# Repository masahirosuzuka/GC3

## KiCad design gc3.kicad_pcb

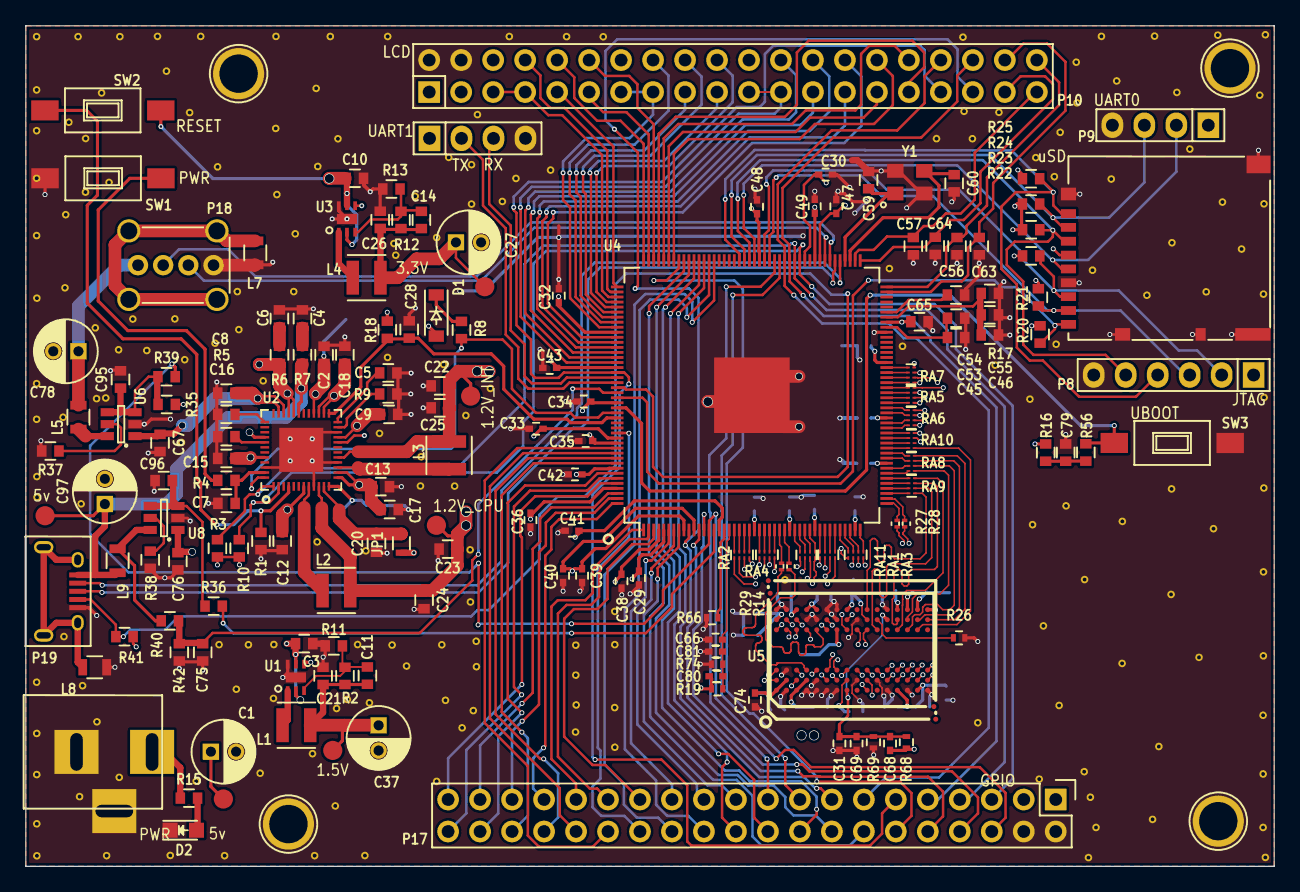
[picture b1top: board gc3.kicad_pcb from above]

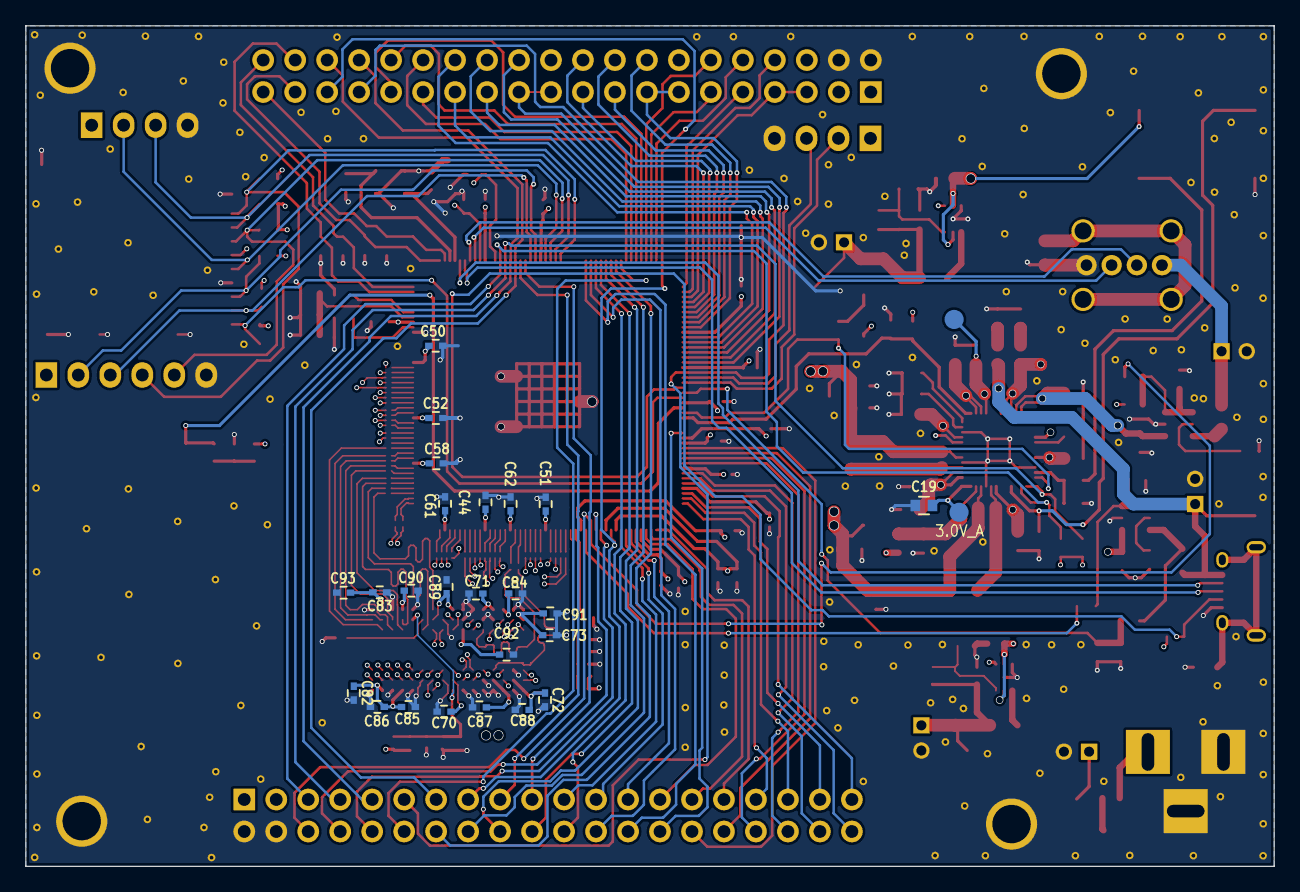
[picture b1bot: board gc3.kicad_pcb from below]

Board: 6 copper layers, 99.1 x 66.8 mm, 191 parts (26 on the bottom side), 225 nets.

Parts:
C1, C27, C37, C78, C97: 100uF; C_Radial_D5_L11_P2
C2, C9, C56, C57, C63, C64, C79: 1uF; Common_0603
C3, C10: 4.7uF; Common_0603
C4, C5, C6, C8, C12, C13, C15, C16, C17, C18, C19, C20, C22, C23, C55: 10uF/6.3V; Common_0603
C7, C24, C25: 1nF; Common_0603
C11, C14: 22pF; Common_0603
C21, C26: 10uF; Common_0603
C28, C67, C75, C76, C95, C96: 0.1uF; Common_0603
C29, C30, C32, C33, C34, C35, C38, C40, C43, C44, C52, C61: 0.1uF/6.3V; C_0402
C31, C47, C66, C68, C69, C70, C71, C72, C73, C74, C80, C81, C83, C84, C85, C86, C88, C89, C90, C91, C92, C93: 0.1uF; C_0402
C36, C39, C41, C48, C50, C58, C62: 10uF/6.3V; C_0402
C42, C49, C51, C82, C87: 22uF/6.3V; C_0402
C45, C46, C53, C54: 0.1uF/6.3V; Common_0603
C59, C60: 30pF; Common_0603
C65: 22uF/6.3V; Common_0603
D1: DIODE; SOD-123
D2: POWER; LED-0805
J1: JACK; BARREL_JACK
J2: DM3AT-SF-PEJM5
JP1: JUMPER; R_0603
L1, L2, L3, L4: 2.2uH; Neosid_Inductor_SMS-ME3015
L5, L7, L8, L9: FB/2A; R_0805
P1, P2, P3, P4, P5, P6, P15: TESTPOINT; Measurement_Point_Round-SMD-Pad_Small
P7: LCD; Pin_Header_Straight_2x20
P8: JTAG; Pin_Header_Straight_1x06
P9: UART0; Pin_Header_Straight_1x04
P10: UART1; Pin_Header_Straight_1x04
P11, P12, P13, P14: GND; 1pin
P16: TEESTPOINT; Measurement_Point_Round-SMD-Pad_Small
P17: GPIO; Pin_Header_Straight_2x20
P18: USB_A; USB_A_Vertical
P19: USB_OTG; USB_Micro-B
R1: 510R; Common_0603
R2: 315k; Common_0603
R3, R10: 2.2k; Common_0603
R4: 1k; Common_0603
R5: 240R/1%; Common_0603
R6, R7: 1R; Common_0603
R8, R18, R20, R21, R22, R23, R24, R25, R35, R41: 47k; Common_0603
R9, R17: 200k/1%; Common_0603
R11: 210k; Common_0603
R12, R36, R39: 100k; Common_0603
R13: 22k; Common_0603
R14, R29: 22R; R_0201
R15: 90R; Common_0603
R16: 100k/1%; Common_0603
R19, R68, R69, R74: 2k/1%; R_0402
R26, R66: 240R/1%; R_0402
R27, R28: 24R; R_0201
R37, R38: 20k; Common_0603
R40: 47K; Common_0603
R42: 100K; Common_0603
R56: 6.8k/1%; Common_0603
RA1, RA2, RA3, RA4, RA5, RA6, RA7, RA8, RA9, RA10, RA11: 22R; EXB18V
SW1: PWR_ON; SW_SPST_FSMSM
SW2: RESET; SW_SPST_FSMSM
SW3: UBOOT; SW_SPST_FSMSM
U1, U3: TPS62290
U2: axp209; TQFP-48-1EP_6x6mm_Pitch0.4mm
U4: a13; LQFP-176_20x20mm_Pitch0.4mm
U5: h5tq2g63bfr; FBGA96(HYNIX_SAMSUNG_512MX16_DDR3)
U6, U8: TPS2552; SOT-23-6
Y1: 24MHz/20pF/20ppm; ecx32

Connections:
1.2V_CPU: C23.1, C24.1, C34.1, C35.1, C36.1, C38.1, C39.1, C40.1, C41.1, C42.1, L2.2, P4.1, U2.10, U4.4, U4.9, U4.11, U4.16, U4.156, U4.164, U4.169, U4.173
1.2V_INT: C22.1, C25.1, C43.1, C44.1, C48.1, C49.1, C50.1, L3.2, P5.1, U2.17, U4.35, U4.73, U4.98, U4.109, U4.149
+1.5V: C11.1, C21.1, C37.1, C51.1, C52.1, C58.1, C61.1, C62.1, C68.1, C70.1, C71.1, C72.1, C73.1, C74.1, C80.1, C82.1, C83.1, C84.1, C85.1, C86.1, C87.1, C88.1, C89.1, C90.1, C91.1, C92.1, C93.1, L1.2, P6.1, R2.1, R19.1, R68.1, U4.23, U4.30, U4.43, U4.53, U4.62, U5.A1, U5.A8, U5.B2, U5.C1, U5.C9, U5.D2, U5.D9, U5.E9, U5.G7, U5.H2, U5.H9, U5.K2, U5.K8, U5.N1, U5.N9, U5.R1, U5.R9
+3.0VA: C19.2, C65.1, P3.1, R16.2, U1.4, U2.12, U4.81
+3V3: C14.1, C26.1, C27.1, C29.1, C30.1, C32.1, C33.1, C47.1, D1.2, J2.4, JP1.1, L4.2, P7.3, P8.1, P9.1, P10.1, P15.1, P17.3, R3.2, R10.2, R12.1, R18.2, R20.1, R21.1, R22.1, R23.1, R24.1, R25.1, R35.2, R41.1, U4.5, U4.97, U4.100, U4.142, U4.163
+5V: C1.1, J1.1, P7.1, P16.1, P17.1, R6.1, R15.1, U2.32, U2.33
/3V3_WIFI: C16.2, U2.41
/+5V_USB_OTG: C97.1, L9.2, P1.1, P19.1, R7.1, U2.31
/EXTEN: U2.20, U3.4
/NMI_N: R8.1, U2.48, U4.158
/RESET_N: C28.1, R18.1, U2.25, U4.159
/VDD_RTC: C18.2, P2.1, U2.28
/VINT: C2.1, U2.26, U2.27
/mpu_ddr3/A0: RA6.5, U5.N3
/mpu_ddr3/A1: RA8.7, U5.P7
/mpu_ddr3/A2: RA5.7, U5.P3
/mpu_ddr3/A3: RA5.8, U5.N2
/mpu_ddr3/A4: RA8.8, U5.P8
/mpu_ddr3/A5: RA5.6, U5.P2
/mpu_ddr3/A6: RA8.6, U5.R8
/mpu_ddr3/A7: RA7.6, U5.R2
/mpu_ddr3/A8: RA8.5, U5.T8
/mpu_ddr3/A9: RA7.8, U5.R3
/mpu_ddr3/A10: RA9.7, U5.L7
/mpu_ddr3/A11: RA10.8, U5.R7
/mpu_ddr3/A12: RA9.5, U5.N7
/mpu_ddr3/A13: RA5.5, U5.T3
/mpu_ddr3/BA0: RA6.6, U5.M2
/mpu_ddr3/BA1: RA9.6, U5.N8
/mpu_ddr3/BA2: RA6.7, U5.M3
/mpu_ddr3/CAS: RA10.5, U5.K3
/mpu_ddr3/CKE: RA9.8, U5.K9
/mpu_ddr3/CK_N: R28.1, U5.K7
/mpu_ddr3/CK_P: R27.1, U5.J7
/mpu_ddr3/D0: RA2.1, U5.E3
/mpu_ddr3/D1: RA3.8, U5.F7
/mpu_ddr3/D2: RA2.2, U5.F2
/mpu_ddr3/D3: RA3.7, U5.F8
/mpu_ddr3/D4: RA2.4, U5.H3
/mpu_ddr3/D5: RA3.5, U5.H8
/mpu_ddr3/D6: RA2.3, U5.G2
/mpu_ddr3/D7: RA3.6, U5.H7
/mpu_ddr3/D8: RA1.7, U5.D7
/mpu_ddr3/D9: RA4.7, U5.C3
/mpu_ddr3/D10: RA1.5, U5.C8
/mpu_ddr3/D11: RA4.8, U5.C2
/mpu_ddr3/D12: RA1.8, U5.A7
/mpu_ddr3/D13: RA4.6, U5.A2
/mpu_ddr3/D14: RA1.6, U5.B8
/mpu_ddr3/D15: RA4.5, U5.A3
/mpu_ddr3/DM0: R14.1, U5.E7
/mpu_ddr3/DM1: R29.1, U5.D3
/mpu_ddr3/DQS0_N: RA11.7, U5.G3
/mpu_ddr3/DQS0_P: RA11.8, U5.F3
/mpu_ddr3/DQS1_N: RA11.5, U5.B7
/mpu_ddr3/DQS1_P: RA11.6, U5.C7
/mpu_ddr3/LCD_CLK: P7.31, U4.129
/mpu_ddr3/LCD_D2: P7.21, P7.23, U4.148
/mpu_ddr3/LCD_D3: P7.24, U4.147
/mpu_ddr3/LCD_D4: P7.25, U4.146
/mpu_ddr3/LCD_D5: P7.26, U4.145
/mpu_ddr3/LCD_D6: P7.27, U4.144
/mpu_ddr3/LCD_D7: P7.28, U4.143
/mpu_ddr3/LCD_D10: P7.13, P7.15, U4.141
/mpu_ddr3/LCD_D11: P7.16, U4.140
/mpu_ddr3/LCD_D12: P7.17, U4.139
/mpu_ddr3/LCD_D13: P7.18, U4.138
/mpu_ddr3/LCD_D14: P7.19, U4.137
/mpu_ddr3/LCD_D15: P7.20, U4.136
/mpu_ddr3/LCD_D18: P7.5, P7.7, U4.135
/mpu_ddr3/LCD_D19: P7.8, U4.134
/mpu_ddr3/LCD_D20: P7.9, U4.133
/mpu_ddr3/LCD_D21: P7.10, U4.132
/mpu_ddr3/LCD_D22: P7.11, U4.131
/mpu_ddr3/LCD_D23: P7.12, U4.130
/mpu_ddr3/LCD_DE: P7.32, U4.128
/mpu_ddr3/LCD_HSYNC: P7.29, U4.127
/mpu_ddr3/LCD_VSYNC: P7.30, U4.126
/mpu_ddr3/ODT: RA7.5, U5.K1
/mpu_ddr3/PIN6/PWM0: P7.36, P17.9, U4.103
/mpu_ddr3/PIN7: P7.33, P17.11, U4.150
/mpu_ddr3/PIN8: P7.34, P17.13, U4.104
/mpu_ddr3/PIN9: P7.35, P17.15, U4.10
/mpu_ddr3/PIN10/TWI1-SCK: P17.17, U4.105
/mpu_ddr3/PIN11/TWI1-SDA: P17.19, U4.106
/mpu_ddr3/PIN12/NWE: P17.21, U4.8
/mpu_ddr3/PIN13/NALE: P17.23, U4.7
/mpu_ddr3/PIN14/NCLE: P17.25, U4.6
/mpu_ddr3/PIN15/NCE1: P17.27, U4.3
/mpu_ddr3/PIN16/NCE0: P17.29, U4.2
/mpu_ddr3/PIN17/NRE: P17.31, U4.1
/mpu_ddr3/PIN18/NRB0: P17.33, U4.176
/mpu_ddr3/PIN19/NRB1: P17.35, U4.175
/mpu_ddr3/PIN20/NDQ0: P17.37, U4.174
/mpu_ddr3/PIN21/NDQ1: P17.39, U4.172
/mpu_ddr3/PIN22/NDQ2: P17.40, U4.171
/mpu_ddr3/PIN23/NDQ3: P17.38, U4.170
/mpu_ddr3/PIN24/NDQ4: P17.36, U4.168
/mpu_ddr3/PIN25/NDQ5: P17.34, U4.167
/mpu_ddr3/PIN26/NDQ6: P17.32, U4.166
/mpu_ddr3/PIN27/NDQ7: P17.30, U4.165
/mpu_ddr3/PIN28/NDQS: P17.28, U4.162
/mpu_ddr3/PIN29: P17.26, U4.118
/mpu_ddr3/PIN30: P17.24, U4.119
/mpu_ddr3/PIN31: P17.22, U4.120
/mpu_ddr3/PIN32: P17.20, U4.121
/mpu_ddr3/PIN33: P17.18, U4.122
/mpu_ddr3/PIN34: P17.16, U4.123
/mpu_ddr3/PIN35: P17.14, U4.124
/mpu_ddr3/PIN36: P17.12, U4.125
/mpu_ddr3/PIN37: P17.10, U4.12
/mpu_ddr3/PIN38/VGA_DIS: P17.8, U4.13
/mpu_ddr3/PIN39/USBH_EN: P17.6, R39.2, U4.14
/mpu_ddr3/RAS: RA10.6, U5.J3
/mpu_ddr3/RESET: RA7.7, U5.T2
/mpu_ddr3/SA0: RA6.4, U4.64
/mpu_ddr3/SA1: RA8.2, U4.52
/mpu_ddr3/SA2: RA5.2, U4.66
/mpu_ddr3/SA3: RA5.1, U4.65
/mpu_ddr3/SA4: RA8.1, U4.51
/mpu_ddr3/SA5: RA5.3, U4.67
/mpu_ddr3/SA6: RA8.3, U4.54
/mpu_ddr3/SA7: RA7.3, U4.71
/mpu_ddr3/SA8: RA8.4, U4.55
/mpu_ddr3/SA9: RA7.1, U4.69
/mpu_ddr3/SA10: RA9.2, U4.48
/mpu_ddr3/SA11: RA10.1, U4.56
/mpu_ddr3/SA12: RA9.4, U4.50
/mpu_ddr3/SA13: RA5.4, U4.68
/mpu_ddr3/SA14: RA10.2, U4.57
/mpu_ddr3/SBA0: RA6.3, U4.63
/mpu_ddr3/SBA1: RA9.3, U4.49
/mpu_ddr3/SBA2: RA6.2, U4.61
/mpu_ddr3/SCAS: RA10.4, U4.59
/mpu_ddr3/SCKE: RA9.1, U4.47
/mpu_ddr3/SCK_N: R28.2, U4.46
/mpu_ddr3/SCK_P: R27.2, U4.45
/mpu_ddr3/SD0: RA2.8, U4.22
/mpu_ddr3/SD0_CARD_DETECT: J2.9, R20.2, U4.155
/mpu_ddr3/SD1: RA3.1, U4.40
/mpu_ddr3/SD2: RA2.7, U4.21
/mpu_ddr3/SD3: RA3.2, U4.41
/mpu_ddr3/SD4: RA2.5, U4.19
/mpu_ddr3/SD5: RA3.4, U4.44
/mpu_ddr3/SD6: RA2.6, U4.20
/mpu_ddr3/SD7: RA3.3, U4.42
/mpu_ddr3/SD8: RA1.2, U4.37
/mpu_ddr3/SD9: RA4.2, U4.25
/mpu_ddr3/SD10: RA1.4, U4.39
/mpu_ddr3/SD11: RA4.1, U4.24
/mpu_ddr3/SD12: RA1.1, U4.36
/mpu_ddr3/SD13: RA4.3, U4.26
/mpu_ddr3/SD14: RA1.3, U4.38
/mpu_ddr3/SD15: RA4.4, U4.27
/mpu_ddr3/SDC0_CMD: J2.3, P8.5, R23.2, U4.111
/mpu_ddr3/SDC0_DATA0: J2.7, P8.2, R22.2, U4.108
/mpu_ddr3/SDC0_DATA1: J2.8, P8.3, R21.2, U4.107
/mpu_ddr3/SDC0_DATA2: J2.1, P8.4, R25.2, U4.113
/mpu_ddr3/SDC0_DATA3: J2.2, P9.3, R24.2, U4.112
/mpu_ddr3/SDC0_SCK: J2.5, P9.2, U4.110
/mpu_ddr3/SDM0: R14.2, U4.29
/mpu_ddr3/SDM1: R29.2, U4.28
/mpu_ddr3/SDQS0_N: RA11.2, U4.32
/mpu_ddr3/SDQS0_P: RA11.1, U4.31
/mpu_ddr3/SDQS1_N: RA11.4, U4.34
/mpu_ddr3/SDQS1_P: RA11.3, U4.33
/mpu_ddr3/SODT: RA7.4, U4.72
/mpu_ddr3/SRAS: RA10.3, U4.58
/mpu_ddr3/SRESET: RA7.2, U4.70
/mpu_ddr3/SVREF: C66.2, C80.2, C81.1, R19.2, R74.1, U4.18
/mpu_ddr3/SWE: RA6.1, U4.60
/mpu_ddr3/TPX1: C64.1, P7.37, U4.89
/mpu_ddr3/TPX2: C63.1, P7.38, U4.87
/mpu_ddr3/TPY1: C57.1, P7.39, U4.90
/mpu_ddr3/TPY2: C56.1, P7.40, U4.88
/mpu_ddr3/UART1_RX: P10.3, U4.151
/mpu_ddr3/UART1_TX: P10.2, U4.152
/mpu_ddr3/UBOOT: R56.1, SW3.2, U4.157
/mpu_ddr3/UDM0: P19.2, U4.93
/mpu_ddr3/UDM1: P18.2, U4.95
/mpu_ddr3/UDP0: P19.3, U4.94
/mpu_ddr3/UDP1: P18.3, U4.96
/mpu_ddr3/USB0_DRV: R36.2, U4.15
/mpu_ddr3/USB0_IDDET: P19.4, R41.2, U4.153
/mpu_ddr3/USB0_VBUSDET: C75.1, R40.2, R42.1, U4.154
/mpu_ddr3/VREF: C31.1, C68.2, C69.1, R68.2, R69.1, U5.H1, U5.M8
/mpu_ddr3/WE: RA6.8, U5.L3
GND: C1.2, C2.2, C3.2, C4.2, C5.2, C6.2, C7.2, C8.2, C9.2, C10.2, C12.1, C13.1, C15.1, C16.1, C17.1, C18.1, C19.1, C20.1, C21.2, C22.2, C23.2, C24.2, C25.2, C26.2, C27.2, C28.2, C29.2, C30.2, C31.2, C32.2, C33.2, C34.2, C35.2, C36.2, C37.2, C38.2, C39.2, C40.2, C41.2, C42.2, C43.2, C44.2, C45.2, C46.2, C47.2, C48.2, C49.2, C50.2, C51.2, C52.2, C53.2, C54.2, C55.2, C56.2, C57.2, C58.2, C59.2, C60.2, C61.2, C62.2, C63.2, C64.2, C65.2, C66.1, C67.2, C69.2, C70.2, C71.2, C72.2, C73.2, C74.2, C75.2, C76.2, C78.2, C79.2, C81.2, C82.2, C83.2, C84.2, C85.2, C86.2, C87.2, C88.2, C89.2, C90.2, C91.2, C92.2, C93.2, C95.2, C96.2, C97.2, D2.1, J1.2, J1.3, J2.6, J2.10, J2.11, L7.1, L8.1, P7.2, P7.4, P8.6, P9.4, P10.4, P11.1, P12.1, P13.1, P14.1, P17.2, P17.4, P18.4, P19.5, R1.2, R5.2, R9.2, R11.2, R13.2, R17.2, R26.2, R37.2, R38.2, R42.2, R66.1, R69.2, R74.2, SW1.1, SW3.1, U1.6, U2.9, U2.16, U2.22, U2.46, U2.49, U3.6, U4.79, U4.177, U5.A9, U5.B1, U5.B3, U5.B9, U5.D1, U5.D8, U5.E1, U5.E2, U5.E8, U5.F1, U5.F9, U5.G1, U5.G8, U5.G9, U5.J2, U5.J8, U5.L2, U5.M1, U5.M9, U5.P1, U5.P9, U5.T1, U5.T9, U6.2, U8.2, Y1.2, Y1.4
IPSOUT: C3.1, C8.1, C9.1, C10.1, C12.2, C13.2, C15.2, C17.2, C67.1, C76.1, SW2.1, U1.2, U1.5, U2.7, U2.13, U2.14, U2.21, U2.34, U2.35, U2.40, U2.44, U3.2, U3.5, U6.1, U8.1
unnamed: C4.1, R7.2
unnamed: C5.1, U2.24
unnamed: C6.1, R6.2
unnamed: C7.1, R4.1, U2.47
unnamed: C11.2, R2.2, R11.1, U1.3
unnamed: C14.2, R12.2, R13.1, U3.3
unnamed: C20.2, JP1.2, U2.11
unnamed: C45.1, C53.1, U4.80
unnamed: C46.1, C55.1, R17.1, U4.82
unnamed: C54.1, U4.83
unnamed: C59.1, U4.92, Y1.1
unnamed: C60.1, U4.91, Y1.3
unnamed: C78.1, L5.2, P18.1
unnamed: C79.1, R16.1, R56.2
unnamed: C95.1, R35.1, R39.1, U6.3, U6.4
unnamed: C96.1, R36.1, U8.3, U8.4
unnamed: D1.1, R8.2
unnamed: D2.2, R15.2
unnamed: L1.1, U1.1
unnamed: L2.1, U2.8
unnamed: L3.1, U2.15
unnamed: L4.1, U3.1
unnamed: L5.1, U6.6
unnamed: L7.2, P18.5
unnamed: L8.2, P19.6
unnamed: L9.1, R40.1, U8.6
unnamed: R1.1, SW2.2, U2.4
unnamed: R4.2, SW1.2
unnamed: R5.1, U2.37
unnamed: R9.1, U2.23
unnamed: R26.1, U5.L8
unnamed: R37.1, U6.5
unnamed: R38.1, U8.5
unnamed: R66.2, U4.17
PIN4/TWI0-SCK: P17.5, R10.1, U2.2, U4.101
PIN5/TWI0-SDA: P17.7, R3.1, U2.1, U4.102

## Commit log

2015-10-07 clean sch and add resistor array
2016-04-02 commit before cleanup all footprint
2016-04-03 clean: all footprint
2016-04-24 GC3-Update3
2016-07-31 Fix : bug fix
2016-09-02 Temp : Temp commit for before Update4
2016-09-24 Temp : temo commit for finish DDR3 routing
2016-10-02 Temp : temp commit, finish routing for Update4
2016-10-10 Add : finish Update$
2016-11-20 Commit before production Update4
2016-12-10 temp : commit before change 8 layer
2017-02-17 Fix : fix line width for impedance matching
2017-02-18 Hotfix : Fix solid ground issue
2017-02-18 Hotfix : Fix solid ground issue panelize
2017-03-01 Temp : temp commit before fix 100uF capacitor pads
